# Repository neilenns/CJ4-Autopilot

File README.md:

# KiBot CI/CD template repository for KiCad 6

This repository provides a ready-to-go CI/CD workflow for KiCad 6 with GitHub actions. Using KiCad5? [See my other repo](https://github.com/neilenns/KiBot-CICD-Template).

## Features of this repository template

1. Integration with GitHub releases to automatically produce documentation and
   fabrication files on every GitHub release, including automatic date and version
   stamping of schematics and PCBs.
2. KiBot preflighting on every pull request (ERC/DRC checks disabled by default).
3. VSCode dev container and default build task for easy local testing of KiBot scripts.

## Creating your GitHub repo and KiCad project

To create a KiCad project using this GitHub template:

1. Hit the _Use this template_ button then follow the steps from GitHub to create a copy of the repo. **The repository name must exactly match the name of the KiCad project.
   Do not use spaces in either the repository or the project name.**
2. Clone the new repo locally.
3. Go to _File_ > _New_ > _Project..._ in KiCad.
4. Name the project the exact same name as the GitHub repository name.
5. Uncheck the _Create a new directory for this project_ option. **This is very important!**
6. Save the project into the top level of the folder for the GitHub repository.

Do not use spaces in the GitHub repository or KiCad project name. Use underscores or hyphens instead, for example `TBM930_De-Ice_-_Panel` or `Collins-FMS-3000`.

If you've done all the steps correctly the folder structure will look similar like this:

Notice that the folder name (which is also the GitHub repo name) and project name are exactly the same and there are no spaces.

## Setting up date and version number replacement

The GitHub automation can automatically set the date and version number in the generated schematic and PCBs. Before using this make sure
to set the timezone to your local timezone in the `.github\workflows\documentation-only.yml` and `.github\workflows\release.yml` files.

Version number and date replacement is done on the `%%version%%` and `%%date%%` string wherever they appear in your `.sch` and `.kicad_pcb` files.
Typically you will use them in the _Page settings_ dialog for the schematic and as text in silkscreen and/or copper layers on your board:

## Documentation generated

The following documents are generated on every release build:

- Interactive BOM - HTML
- Schematic - PDF
- PCB front copper and explanatory drawings layers - PDF
- PCB back copper and explanatory drawings layers - PDF
- 3D render - STEP
- PCB front - JPEG
- PCB back - JPEG

These documents can also be generated by manually running the `KiBot - Generate documentation` action on GitHub.

## Fabrication files generated

The following fabrication files are generated on every release build:

- JLCPCB gerbers and drill files, with BOM and placement files for SMT service
- PCBWay gerbers and drill files

The fabrication files can also be generated by manually running the `KiBot - Release` action on GitHub.

## How this works

A complete CodeTour is included in this repository that walks through all the components
of how KiBot scripts and GitHub actions work. [Use github.dev to view the CodeTour](https://github.dev/neilenns/KiBot-CICD-Template)!

## Running builds locally

This repository template includes the files necessary to run in a VSCode dev container,
which dramatically reduces the effort required to use KiBot on Windows machines.

Never used VSCode remote containers before on Windows? Here's how to get set up:

1. From a PowerShell install WSL2 with this command: `wsl --install`
2. Install [Visual Studio Code](https://code.visualstudio.com/Download) and Docker Desktop(https://www.docker.com/products/docker-desktop)
3. Install the [Remote Containers](https://marketplace.visualstudio.com/items?itemName=ms-vscode-remote.remote-containers) extension for VSCode

When installing Docker Desktop you may be told you have to enable virtualization in your computer's BIOS. Setting that up
is outside the scope of this readme but isn't hard. Just do a web search for your motherboard for how to enter the BIOS
and what the exact name of the setting is, then turn it on.

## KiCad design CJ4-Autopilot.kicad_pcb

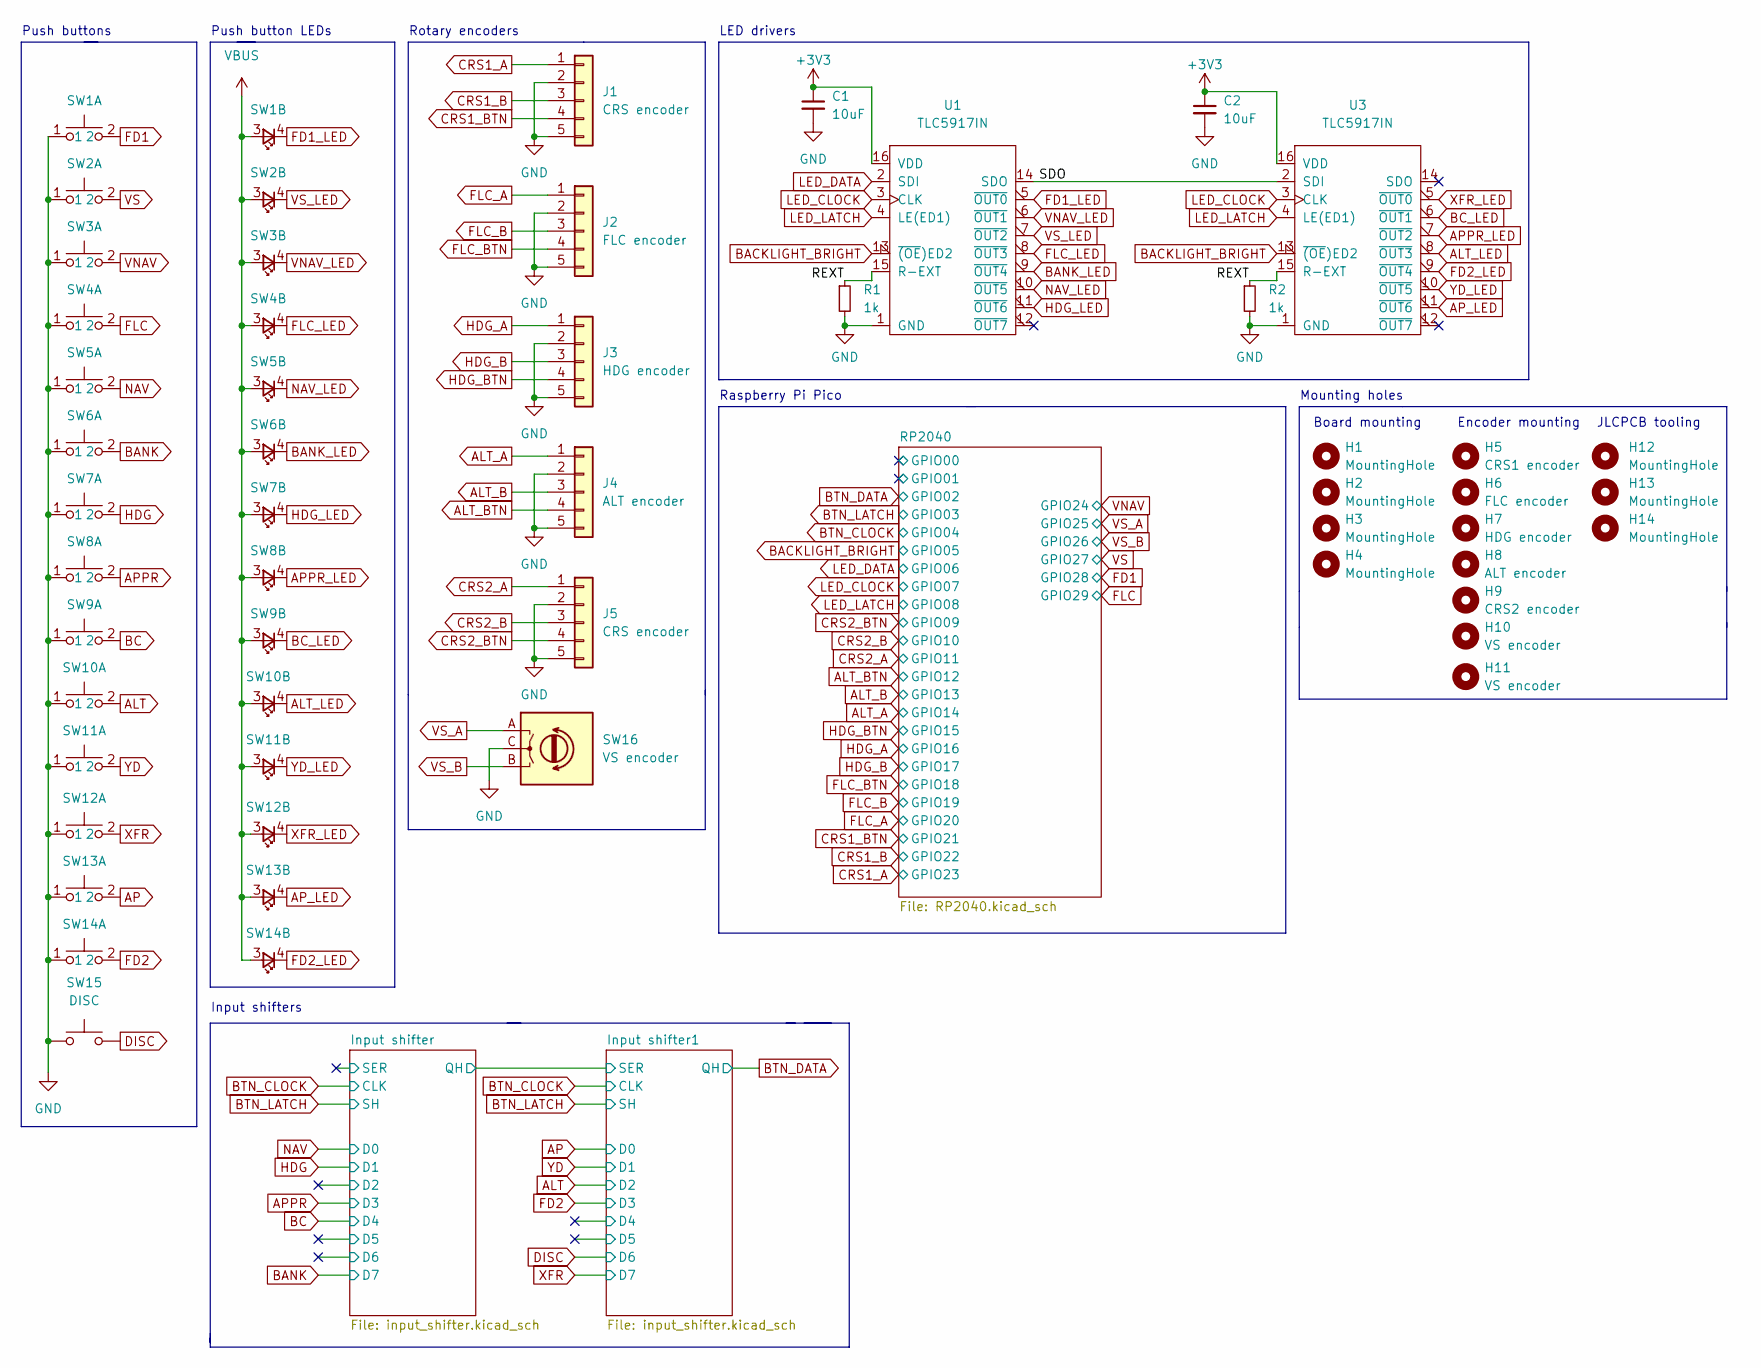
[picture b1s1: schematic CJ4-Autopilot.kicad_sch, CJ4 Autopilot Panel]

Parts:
C1, C2: 10uF; C_0603_1608Metric; JLC 0603
H1, H2, H3, H4: MountingHole; MountingHole_3.2mm_M3
H5: CRS1 encoder; EN11-HSM1BF20 panel mount
H6: FLC encoder; EN11-HSM1BF20 panel mount
H7: HDG encoder; EN11-HSM1BF20 panel mount
H8: ALT encoder; EN11-HSM1BF20 panel mount
H9: CRS2 encoder; EN11-HSM1BF20 panel mount
H10, H11: VS encoder; MountingHole_3.2mm_M3
H12, H13, H14: MountingHole; JLCPCB_Tooling_Hole
J1, J5: CRS encoder; JST_XH_B5B-XH-A_1x05_P2.50mm_Vertical
J2: FLC encoder; JST_XH_B5B-XH-A_1x05_P2.50mm_Vertical
J3: HDG encoder; JST_XH_B5B-XH-A_1x05_P2.50mm_Vertical
J4: ALT encoder; JST_XH_B5B-XH-A_1x05_P2.50mm_Vertical
R1, R2: 1k; Perfect_0402; JLC 0402
SW1: FD1; SW_PUSH_6mm
SW2: VS; SW_PUSH_6mm
SW3: VNAV; SW_PUSH_6mm
SW4: FLC; SW_PUSH_6mm
SW5: NAV; SW_PUSH_6mm
SW6: BANK; SW_PUSH_6mm
SW7: HDG; SW_PUSH_6mm
SW8: APPR; SW_PUSH_6mm
SW9: BC; SW_PUSH_6mm
SW10: ALT; SW_PUSH_6mm
SW11: YD; SW_PUSH_6mm
SW12: XFR; SW_PUSH_6mm
SW13: AP; SW_PUSH_6mm
SW14: FD2; SW_PUSH_6mm
SW15: DISC; SW_PUSH_6mm
SW16: VS encoder; EN11-VNB1BQ15
U1, U3: TLC5917IN; SOIC-16_3.9x9.9mm_P1.27mm

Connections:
+3V3: C1.1, C2.1, U1.16 (VDD), U3.16 (VDD); also elsewhere on the board
/REXT: R1.1, R2.1, U1.15 (R-EXT), U3.15 (R-EXT)
/SDO: U1.14 (SDO), U3.2 (SDI)
ALT: SW10.2; also elsewhere on the board
ALT_A: J4.1; also elsewhere on the board
ALT_B: J4.3; also elsewhere on the board
ALT_BTN: J4.4; also elsewhere on the board
ALT_LED: SW10.4, U3.8 (~OUT3)
AP: SW13.2; also elsewhere on the board
APPR: SW8.2; also elsewhere on the board
APPR_LED: SW8.4, U3.7 (~OUT2)
AP_LED: SW13.4, U3.11 (~OUT6)
BACKLIGHT_BRIGHT: U1.13 (~(OE)ED2), U3.13 (~(OE)ED2); also elsewhere on the board
BANK: SW6.2; also elsewhere on the board
BANK_LED: SW6.4, U1.9 (~OUT4)
BC: SW9.2; also elsewhere on the board
BC_LED: SW9.4, U3.6 (~OUT1)
CRS1_A: J1.1; also elsewhere on the board
CRS1_B: J1.3; also elsewhere on the board
CRS1_BTN: J1.4; also elsewhere on the board
CRS2_A: J5.1; also elsewhere on the board
CRS2_B: J5.3; also elsewhere on the board
CRS2_BTN: J5.4; also elsewhere on the board
DISC: SW15.2; also elsewhere on the board
FD1: SW1.2; also elsewhere on the board
FD1_LED: SW1.4, U1.5 (~OUT0)
FD2: SW14.2; also elsewhere on the board
FD2_LED: SW14.4, U3.9 (~OUT4)
FLC: SW4.2; also elsewhere on the board
FLC_A: J2.1; also elsewhere on the board
FLC_B: J2.3; also elsewhere on the board
FLC_BTN: J2.4; also elsewhere on the board
FLC_LED: SW4.4, U1.8 (~OUT3)
GND: C1.2, C2.2, J1.2, J1.5, J2.2, J2.5, J3.2, J3.5, J4.2, J4.5, J5.2, J5.5, R1.2, R2.2, SW1.1, SW2.1, SW3.1, SW4.1, SW5.1, SW6.1, SW7.1, SW8.1, SW9.1, SW10.1, SW11.1, SW12.1, SW13.1, SW14.1, SW15.1, SW16.C, U1.1 (GND), U3.1 (GND); also elsewhere on the board
HDG: SW7.2; also elsewhere on the board
HDG_A: J3.1; also elsewhere on the board
HDG_B: J3.3; also elsewhere on the board
HDG_BTN: J3.4; also elsewhere on the board
HDG_LED: SW7.4, U1.11 (~OUT6)
LED_CLOCK: U1.3 (CLK), U3.3 (CLK); also elsewhere on the board
LED_DATA: U1.2 (SDI); also elsewhere on the board
LED_LATCH: U1.4 (LE(ED1)), U3.4 (LE(ED1)); also elsewhere on the board
NAV: SW5.2; also elsewhere on the board
NAV_LED: SW5.4, U1.10 (~OUT5)
VBUS: SW1.3, SW2.3, SW3.3, SW4.3, SW5.3, SW6.3, SW7.3, SW8.3, SW9.3, SW10.3, SW11.3, SW12.3, SW13.3, SW14.3; also elsewhere on the board
VNAV: SW3.2; also elsewhere on the board
VNAV_LED: SW3.4, U1.6 (~OUT1)
VS: SW2.2; also elsewhere on the board
VS_A: SW16.A; also elsewhere on the board
VS_B: SW16.B; also elsewhere on the board
VS_LED: SW2.4, U1.7 (~OUT2)
XFR: SW12.2; also elsewhere on the board
XFR_LED: SW12.4, U3.5 (~OUT0)
YD: SW11.2; also elsewhere on the board
YD_LED: SW11.4, U3.10 (~OUT5)

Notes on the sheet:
JLCPCB tooling
Mounting holes
Input shifters
LED drivers
Board mounting
Rotary encoders
Encoder mounting
Raspberry Pi Pico
Push button LEDs
Push buttons

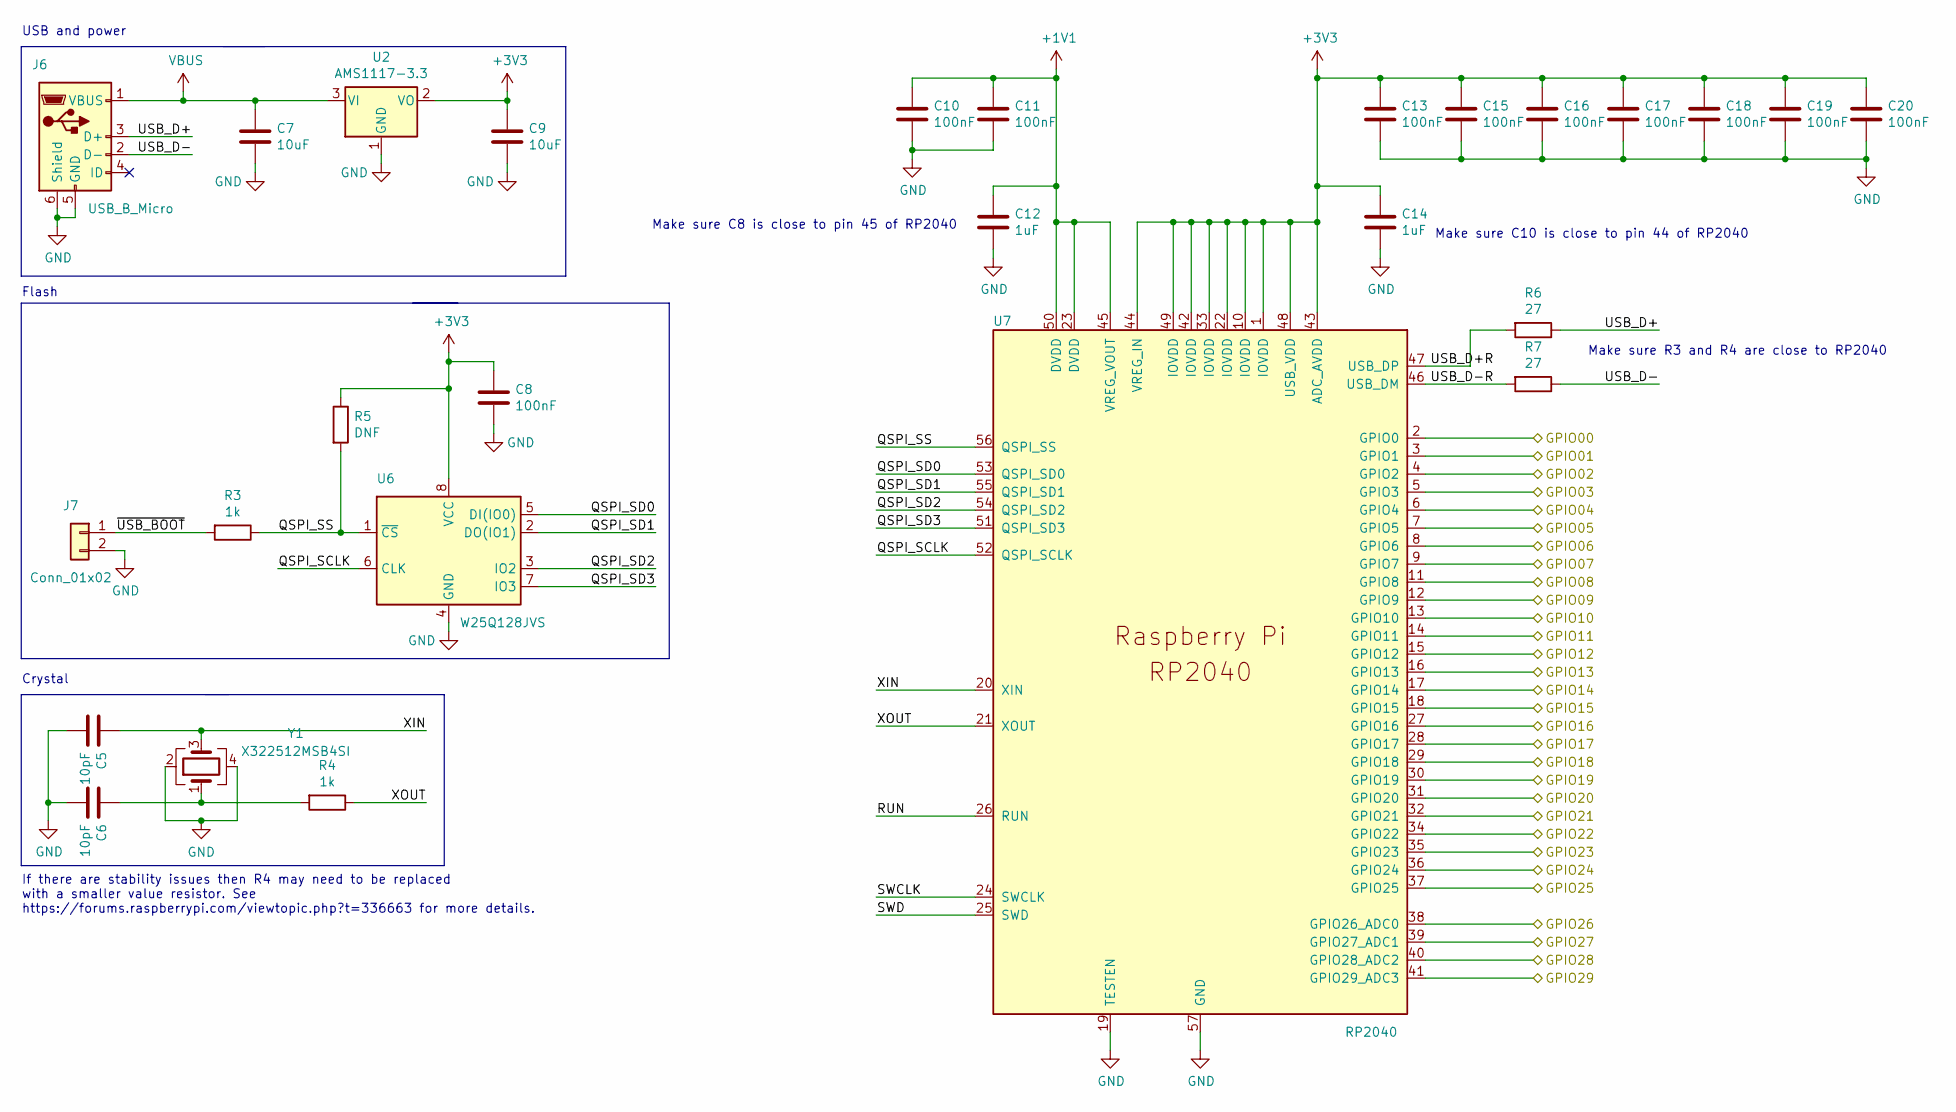
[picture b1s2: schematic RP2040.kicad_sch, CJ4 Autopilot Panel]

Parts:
C5, C6: 10pF; Perfect_0402; JLC 0402
C7, C9: 10uF; C_0603_1608Metric; JLC 0603
C8, C10, C11, C13, C15, C16, C17, C18, C19, C20: 100nF; Perfect_0402; JLC 0402
C12, C14: 1uF; Perfect_0402; JLC 0402
J6: USB_B_Micro; USB_B_Mini_Amphenol_UE25BE5510H
J7: Conn_01x02; PinHeader_1x02_P2.54mm_Vertical
R3, R4: 1k; Perfect_0402; JLC 0402
R5: DNF; R_1206_3216Metric_Pad1.30x1.75mm_HandSolder
R6, R7: 27; R_0603_1608Metric; JLC 0603
U2: AMS1117-3.3; SOT-223-3_TabPin2; JLC SOT-223
U6: W25Q128JVS; SOIC-8_5.23x5.23mm_P1.27mm; JLC SOIC-8_5.3x5.3x1.27P
U7: RP2040; RP2040-QFN-56; JLC LQFN-56_EP_7.0x7.0x0.4P
Y1: X322512MSB4SI; Crystal_SMD_3225-4Pin_3.2x2.5mm; JLC SMD-3225_4P

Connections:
+1V1: C10.1, C11.1, C12.1, U7.23 (DVDD), U7.45 (VREG_VOUT), U7.50 (DVDD)
+3V3: C8.1, C9.1, C13.1, C14.1, C15.1, C16.1, C17.1, C18.1, C19.1, C20.1, R5.1, U2.2 (VO), U6.8 (VCC), U7.1 (IOVDD), U7.10 (IOVDD), U7.22 (IOVDD), U7.33 (IOVDD), U7.42 (IOVDD), U7.43 (ADC_AVDD), U7.44 (VREG_IN), U7.48 (USB_VDD), U7.49 (IOVDD); also elsewhere on the board
/RP2040/GPIO00: U7.2 (GPIO0)
/RP2040/GPIO01: U7.3 (GPIO1)
/RP2040/QSPI_SCLK: U6.6 (CLK), U7.52 (QSPI_SCLK)
/RP2040/QSPI_SD0: U6.5 (DI(IO0)), U7.53 (QSPI_SD0)
/RP2040/QSPI_SD1: U6.2 (DO(IO1)), U7.55 (QSPI_SD1)
/RP2040/QSPI_SD2: U6.3 (IO2), U7.54 (QSPI_SD2)
/RP2040/QSPI_SD3: U6.7 (IO3), U7.51 (QSPI_SD3)
/RP2040/QSPI_SS: R3.1, R5.2, U6.1 (~CS), U7.56 (QSPI_SS)
/RP2040/RUN: U7.26 (RUN)
/RP2040/SWCLK: U7.24 (SWCLK)
/RP2040/SWD: U7.25 (SWD)
/RP2040/USB_D+: J6.3 (D+), R6.1
/RP2040/USB_D+R: R6.2, U7.47 (USB_DP)
/RP2040/USB_D-: J6.2 (D-), R7.1
/RP2040/USB_D-R: R7.2, U7.46 (USB_DM)
/RP2040/XIN: C5.1, U7.20 (XIN), Y1.3
/RP2040/XOUT: R4.1, U7.21 (XOUT)
/RP2040/~USB_BOOT: J7.1, R3.2
ALT_A: U7.17 (GPIO14); also elsewhere on the board
ALT_B: U7.16 (GPIO13); also elsewhere on the board
ALT_BTN: U7.15 (GPIO12); also elsewhere on the board
BACKLIGHT_BRIGHT: U7.7 (GPIO5); also elsewhere on the board
BTN_CLOCK: U7.6 (GPIO4); also elsewhere on the board
BTN_DATA: U7.4 (GPIO2); also elsewhere on the board
BTN_LATCH: U7.5 (GPIO3); also elsewhere on the board
CRS1_A: U7.35 (GPIO23); also elsewhere on the board
CRS1_B: U7.34 (GPIO22); also elsewhere on the board
CRS1_BTN: U7.32 (GPIO21); also elsewhere on the board
CRS2_A: U7.14 (GPIO11); also elsewhere on the board
CRS2_B: U7.13 (GPIO10); also elsewhere on the board
CRS2_BTN: U7.12 (GPIO9); also elsewhere on the board
FD1: U7.40 (GPIO28_ADC2); also elsewhere on the board
FLC: U7.41 (GPIO29_ADC3); also elsewhere on the board
FLC_A: U7.31 (GPIO20); also elsewhere on the board
FLC_B: U7.30 (GPIO19); also elsewhere on the board
FLC_BTN: U7.29 (GPIO18); also elsewhere on the board
GND: C5.2, C6.2, C7.2, C8.2, C9.2, C10.2, C11.2, C12.2, C13.2, C14.2, C15.2, C16.2, C17.2, C18.2, C19.2, C20.2, J6.5 (GND), J6.6 (Shield), J7.2, U2.1 (GND), U6.4 (GND), U7.19 (TESTEN), U7.57 (GND), Y1.2, Y1.4; also elsewhere on the board
HDG_A: U7.27 (GPIO16); also elsewhere on the board
HDG_B: U7.28 (GPIO17); also elsewhere on the board
HDG_BTN: U7.18 (GPIO15); also elsewhere on the board
LED_CLOCK: U7.9 (GPIO7); also elsewhere on the board
LED_DATA: U7.8 (GPIO6); also elsewhere on the board
LED_LATCH: U7.11 (GPIO8); also elsewhere on the board
unnamed: C6.1, R4.2, Y1.1
VBUS: C7.1, J6.1 (VBUS), U2.3 (VI); also elsewhere on the board
VNAV: U7.36 (GPIO24); also elsewhere on the board
VS: U7.39 (GPIO27_ADC1); also elsewhere on the board
VS_A: U7.37 (GPIO25); also elsewhere on the board
VS_B: U7.38 (GPIO26_ADC0); also elsewhere on the board

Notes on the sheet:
USB and power
Crystal
Flash
If there are stability issues then R4 may need to be replaced with a smaller value resistor. See https://forums.raspberrypi.com/viewtopic.php?t=336663 for more details.
Make sure C8 is close to pin 45 of RP2040
Make sure R3 and R4 are close to RP2040
Make sure C10 is close to pin 44 of RP2040

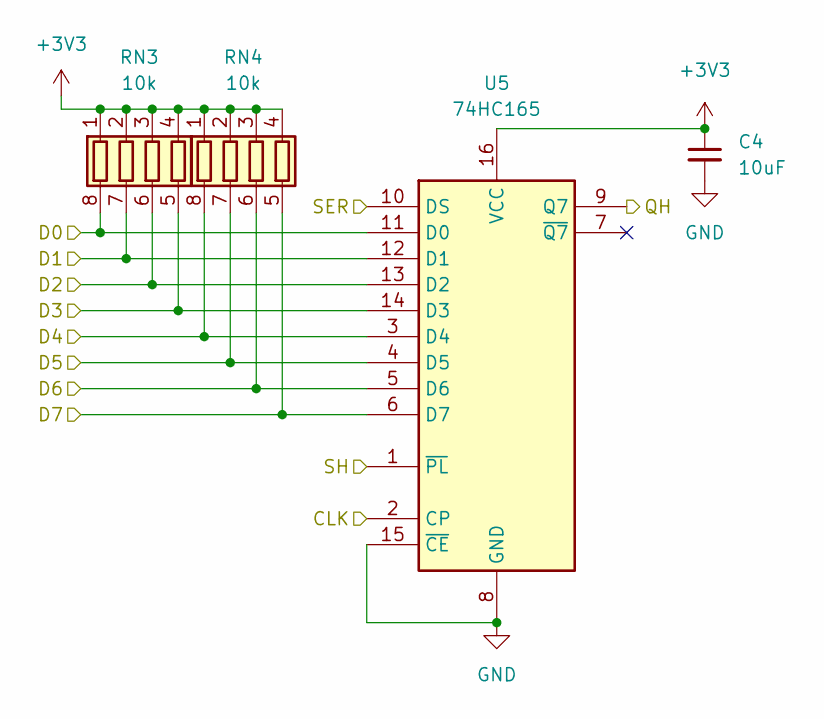
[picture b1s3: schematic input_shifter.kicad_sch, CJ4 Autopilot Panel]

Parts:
C4: 10uF; C_0603_1608Metric; JLC 0603
RN3, RN4: 10k; R_Array_Convex_4x0603; JLC 0603_x4
U5: 74HC165; SOIC-16_3.9x9.9mm_P1.27mm; JLC SOIC-16_3.9x9.9x1.27P

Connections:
+3V3: C4.1, RN3.1 (R1.1), RN3.2 (R2.1), RN3.3 (R3.1), RN3.4 (R4.1), RN4.1 (R1.1), RN4.2 (R2.1), RN4.3 (R3.1), RN4.4 (R4.1), U5.16 (VCC); also elsewhere on the board
/Input shifter1/D4: RN4.8 (R1.2), U5.3 (D4)
/Input shifter1/D5: RN4.7 (R2.2), U5.4 (D5)
/Input shifter/QH: U5.10 (DS); also elsewhere on the board
ALT: RN3.6 (R3.2), U5.13 (D2); also elsewhere on the board
AP: RN3.8 (R1.2), U5.11 (D0); also elsewhere on the board
BTN_CLOCK: U5.2 (CP); also elsewhere on the board
BTN_DATA: U5.9 (Q7); also elsewhere on the board
BTN_LATCH: U5.1 (~PL); also elsewhere on the board
DISC: RN4.6 (R3.2), U5.5 (D6); also elsewhere on the board
FD2: RN3.5 (R4.2), U5.14 (D3); also elsewhere on the board
GND: C4.2, U5.8 (GND), U5.15 (~CE); also elsewhere on the board
XFR: RN4.5 (R4.2), U5.6 (D7); also elsewhere on the board
YD: RN3.7 (R2.2), U5.12 (D1); also elsewhere on the board

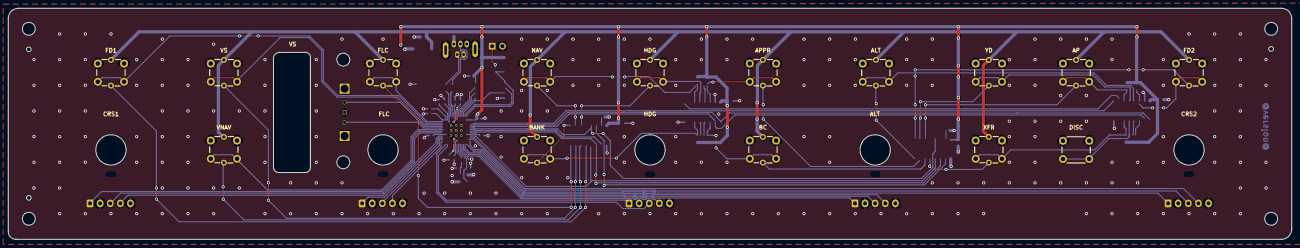
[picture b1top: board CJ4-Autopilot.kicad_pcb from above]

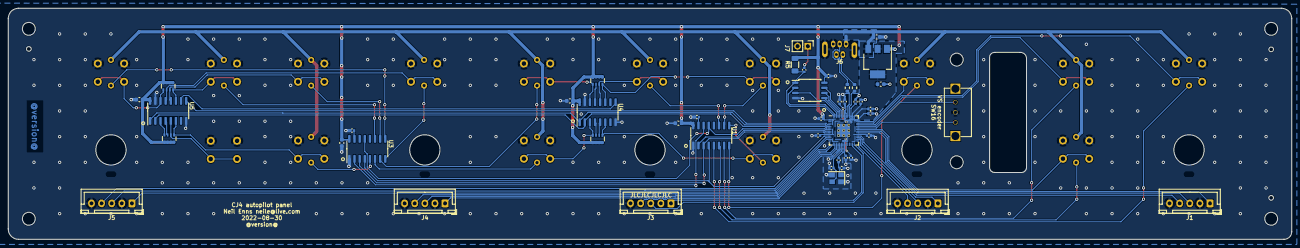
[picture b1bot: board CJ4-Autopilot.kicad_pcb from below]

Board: 2 copper layers, 317.5 x 57.1 mm, 76 parts (47 on the bottom side), 79 nets.

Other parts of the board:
C3: 10uF; C_0603_1608Metric
RN1, RN2: 10k; R_Array_Convex_4x0603
U4: 74HC165; SOIC-16_3.9x9.9mm_P1.27mm

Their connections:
+3V3: C3.1, RN1.1 (R1.1), RN1.2 (R2.1), RN1.3 (R3.1), RN1.4 (R4.1), RN2.1 (R1.1), RN2.2 (R2.1), RN2.3 (R3.1), RN2.4 (R4.1), U4.16 (VCC); also elsewhere on the board
/Input shifter/D2: RN1.6 (R3.2), U4.13 (D2)
/Input shifter/D5: RN2.7 (R2.2), U4.4 (D5)
/Input shifter/D6: RN2.6 (R3.2), U4.5 (D6)
/Input shifter/QH: U4.9 (Q7); also elsewhere on the board
APPR: RN1.5 (R4.2), U4.14 (D3); also elsewhere on the board
BANK: RN2.5 (R4.2), U4.6 (D7); also elsewhere on the board
BC: RN2.8 (R1.2), U4.3 (D4); also elsewhere on the board
BTN_CLOCK: U4.2 (CP); also elsewhere on the board
BTN_LATCH: U4.1 (~PL); also elsewhere on the board
GND: C3.2, U4.8 (GND), U4.15 (~CE); also elsewhere on the board
HDG: RN1.7 (R2.2), U4.12 (D1); also elsewhere on the board
NAV: RN1.8 (R1.2), U4.11 (D0); also elsewhere on the board

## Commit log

2022-08-25 Initial work, lost interest. Bah.
2022-08-25 Added pico
2022-08-26 Full schematic done
2022-08-26 Update .gitignore file
2022-08-26 Update version tag
2022-08-26 Try adding pdf to the release
2022-08-26 Try fixing path
2022-08-26 Initial board layout, still a lot of work to do
2022-08-27 Add RP2040 directly to the board
2022-08-28 RP2040 wired up, warning cleanup
2022-08-28 Update encoder footprint, USB trace width
2022-08-28 Add model for right angle encoder, adjust opening
2022-08-28 All power routed???
2022-08-29 Moved chips, rotated encoder. Lots of traces, it's gonna work!
2022-08-29 Left side fully connected
2022-08-30 Tons and tons of traces
2022-08-30 Fully routed!
2022-08-30 Added 3d models
2022-08-30 Cleanup based on feedback
2022-08-30 Update silkscreen, fix gerber output
2022-08-30 Via stitching, hole cleanup, silkscreen
2022-08-30 Change drill origin
2022-08-30 JLCPCB rotation update, add missing pin 1 indicator
2022-08-30 Fix broken version text, add more vias
2022-08-30 More missing versions
2022-08-31 Add missing net labels
2022-08-31 Update crystal capacitors
2022-08-31 Correct part rotation for crystal with JLCPCB
2022-08-31 Correct RP2040 rotation for JLCPCB
2022-08-31 Fix RP2040 rotation *again*
2022-09-01 Add firmware and config files.
2022-09-01 Change all 3d models to .step
2022-10-01 Tons of 3D designs
2025-02-25 Add renovate.json
